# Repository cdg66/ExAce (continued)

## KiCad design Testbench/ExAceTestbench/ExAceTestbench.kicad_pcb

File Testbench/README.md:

this is asimple board that breakout the SERDES pins out to SMA connectors for easy testing of the interface.

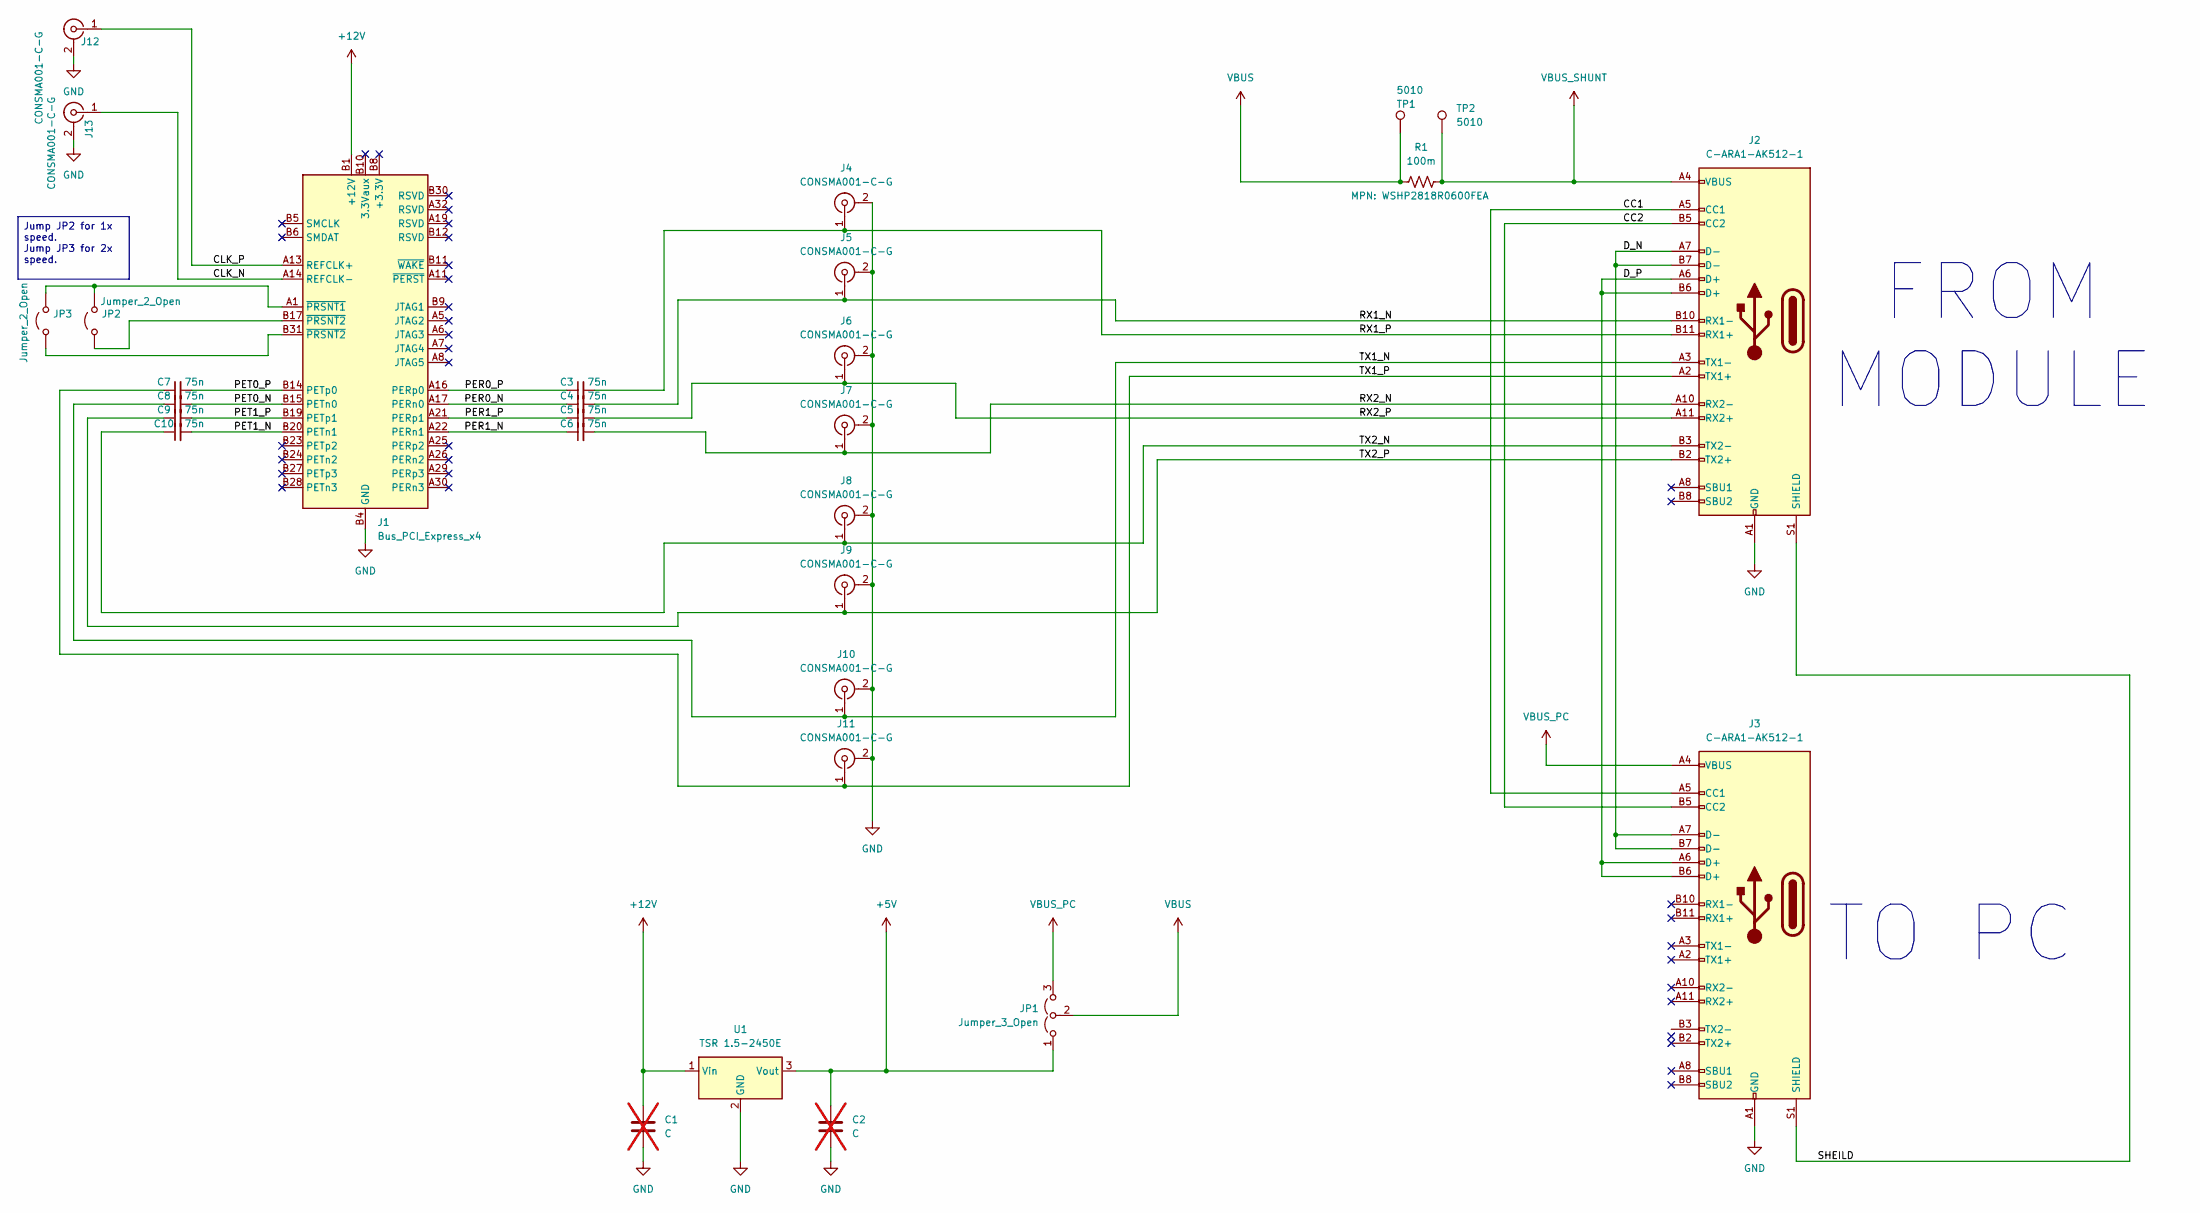
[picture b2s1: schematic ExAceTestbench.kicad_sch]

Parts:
C1, C2: C; C_1206_3216Metric; not fitted
C3, C4, C5, C6, C7, C8, C9, C10: 75n; C_0402_1005Metric
J1: Bus_PCI_Express_x4; BUS_PCIexpress_x4
J2, J3: C-ARA1-AK512-1; USB_C_Receptacle_CNCTech_C-ARA1-AK51X; MPN C-ARA1-AK512-1
J4, J5, J6, J7, J8, J9, J10, J11, J12, J13: CONSMA001-C-G; SMA_Amphenol_901-144_Vertical; MPN CONSMA001-C-G
JP1: Jumper_3_Open; PinHeader_1x03_P2.54mm_Vertical
JP2, JP3: Jumper_2_Open; PinHeader_1x02_P2.54mm_Vertical
R1: 100m; 2818; MPN WSHP2818R0600FEA
TP1, TP2: 5010; TestPoint_Keystone_5010-5014_Multipurpose; MPN 5010
U1: TSR 1.5-2450E; Converter_DCDC_TRACO_TSR-1_THT

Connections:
+5V: C2.1, JP1.1 (A), U1.3 (Vout)
+12V: C1.1, J1.A2 (+12V), J1.A3 (+12V), J1.B1 (+12V), J1.B2 (+12V), J1.B3 (+12V), U1.1 (Vin)
/CC1: J2.A5 (CC1), J3.A5 (CC1)
/CC2: J2.B5 (CC2), J3.B5 (CC2)
/CLK_N: J1.A14 (REFCLK-), J13.1 (In)
/CLK_P: J1.A13 (REFCLK+), J12.1 (In)
/D_N: J2.A7 (D-), J2.B7 (D-), J3.A7 (D-), J3.B7 (D-)
/D_P: J2.A6 (D+), J2.B6 (D+), J3.A6 (D+), J3.B6 (D+)
/PER0_N: C4.1, J1.A17 (PERn0)
/PER0_P: C3.1, J1.A16 (PERp0)
/PER1_N: C6.1, J1.A22 (PERn1)
/PER1_P: C5.1, J1.A21 (PERp1)
/PET0_N: C8.2, J1.B15 (PETn0)
/PET0_P: C7.2, J1.B14 (PETp0)
/PET1_N: C10.2, J1.B20 (PETn1)
/PET1_P: C9.2, J1.B19 (PETp1)
/RX1_N: C4.2, J2.B10 (RX1-), J5.1 (In)
/RX1_P: C3.2, J2.B11 (RX1+), J4.1 (In)
/RX2_N: C6.2, J2.A10 (RX2-), J7.1 (In)
/RX2_P: C5.2, J2.A11 (RX2+), J6.1 (In)
/SHEILD: J2.S1 (SHIELD), J3.S1 (SHIELD)
/TX1_N: C8.1, J2.A3 (TX1-), J10.1 (In)
/TX1_P: C7.1, J2.A2 (TX1+), J11.1 (In)
/TX2_N: C10.1, J2.B3 (TX2-), J8.1 (In)
/TX2_P: C9.1, J2.B2 (TX2+), J9.1 (In)
GND: C1.2, C2.2, J1.A4 (GND), J1.A12 (GND), J1.A15 (GND), J1.A18 (GND), J1.A20 (GND), J1.A23 (GND), J1.A24 (GND), J1.A27 (GND), J1.A28 (GND), J1.A31 (GND), J1.B4 (GND), J1.B7 (GND), J1.B13 (GND), J1.B16 (GND), J1.B18 (GND), J1.B21 (GND), J1.B22 (GND), J1.B25 (GND), J1.B26 (GND), J1.B29 (GND), J1.B32 (GND), J2.A1 (GND), J2.A12 (GND), J2.B1 (GND), J2.B12 (GND), J3.A1 (GND), J3.A12 (GND), J3.B1 (GND), J3.B12 (GND), J4.2 (Ext), J5.2 (Ext), J6.2 (Ext), J7.2 (Ext), J8.2 (Ext), J9.2 (Ext), J10.2 (Ext), J11.2 (Ext), J12.2 (Ext), J13.2 (Ext), U1.2 (GND)
unnamed: J1.A1 (~PRSNT1), JP2.2 (B), JP3.2 (B)
unnamed: J1.B17 (~PRSNT2), JP2.1 (A)
unnamed: J1.B31 (~PRSNT2), JP3.1 (A)
VBUS: JP1.2 (C), R1.1, TP1.1
VBUS_PC: J3.A4 (VBUS), J3.A9 (VBUS), J3.B4 (VBUS), J3.B9 (VBUS), JP1.3 (B)
VBUS_SHUNT: J2.A4 (VBUS), J2.A9 (VBUS), J2.B4 (VBUS), J2.B9 (VBUS), R1.2, TP2.1

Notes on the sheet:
FROM MODULE
TO PC
Jump JP2 for 1x speed. Jump JP3 for 2x speed.

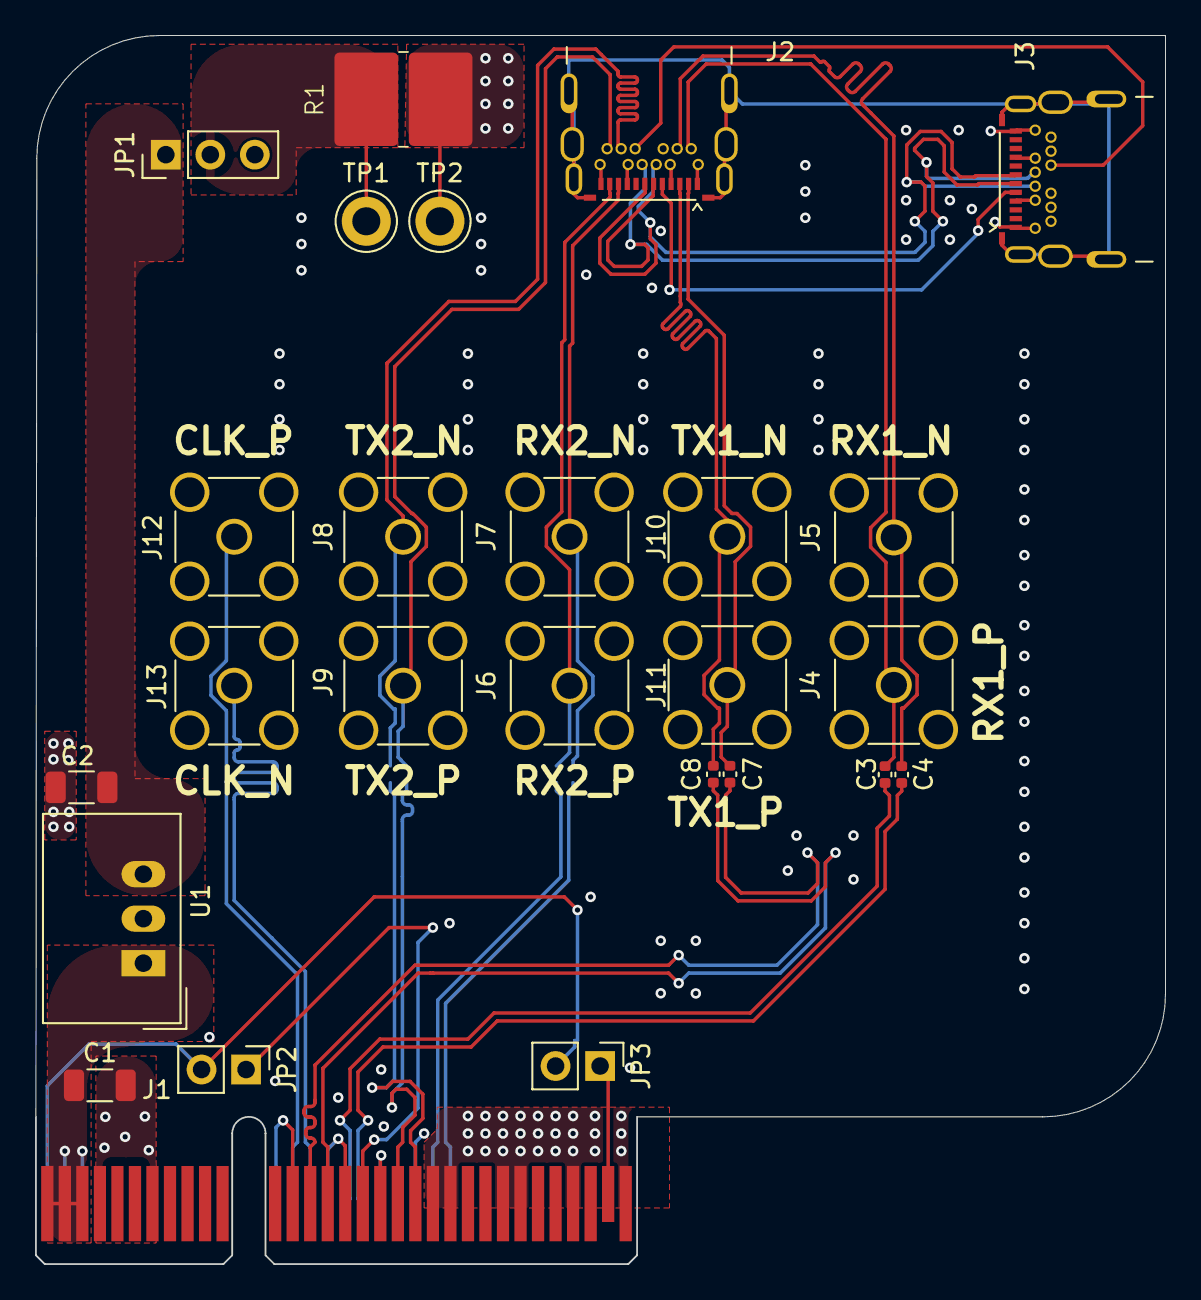
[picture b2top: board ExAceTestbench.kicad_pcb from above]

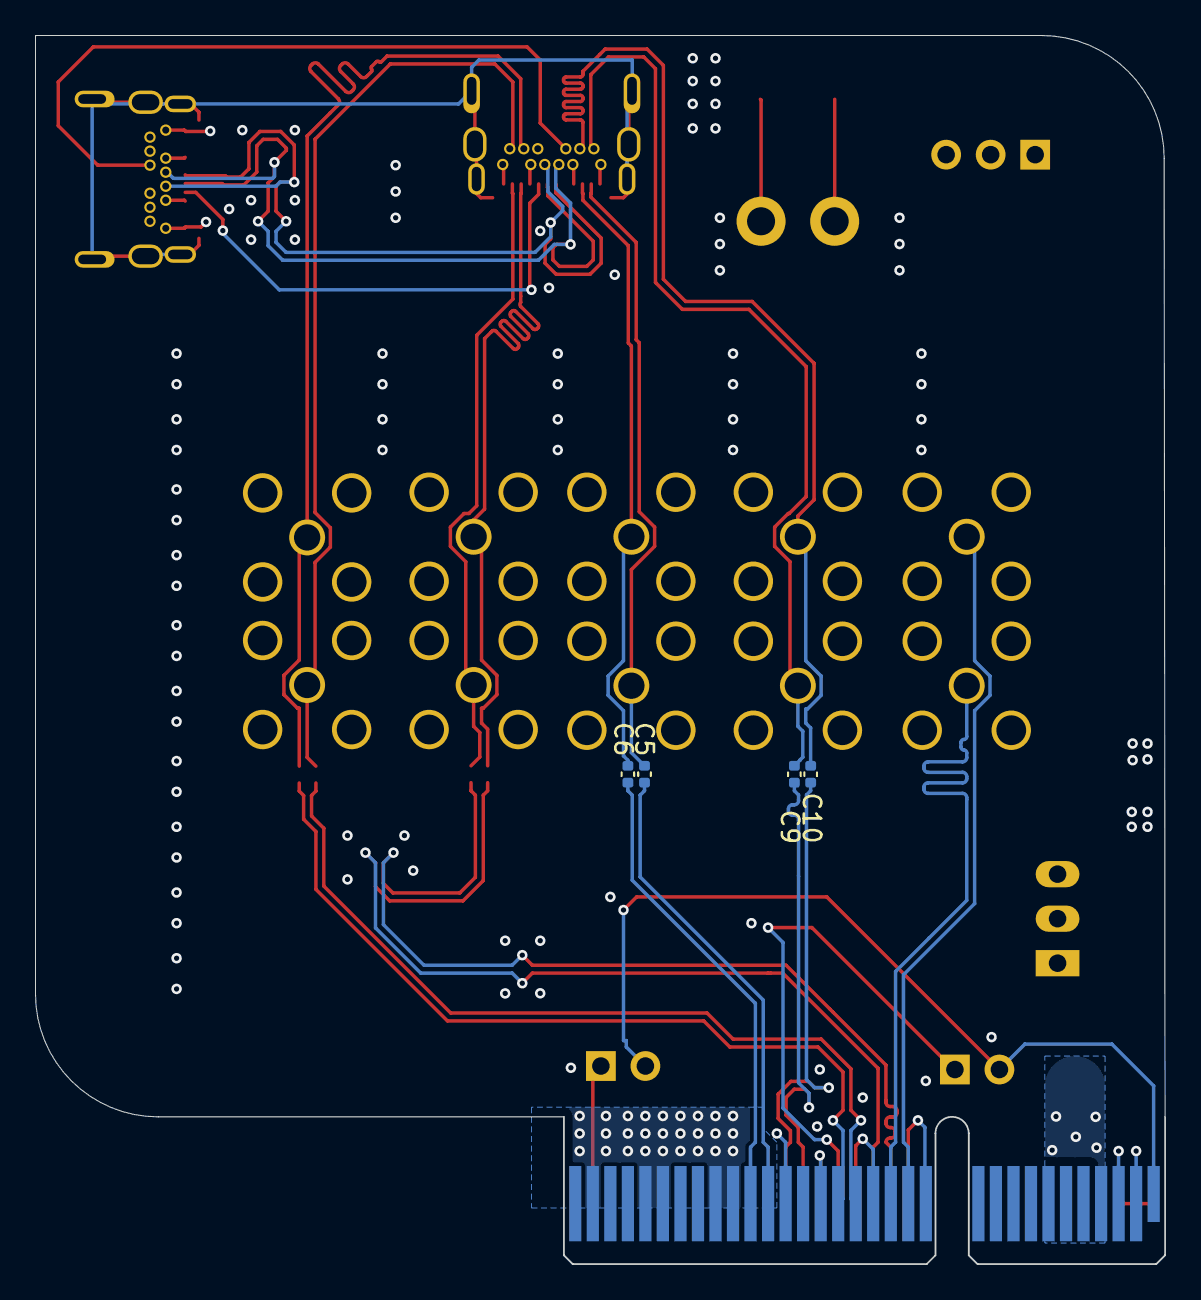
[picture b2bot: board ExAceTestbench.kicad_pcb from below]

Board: 4 copper layers, 64.5 x 70.1 mm, 30 parts (4 on the bottom side), 32 nets.

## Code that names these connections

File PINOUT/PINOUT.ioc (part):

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Mcu.Name=STM32L422RBIx
Mcu.Package=UFBGA64
Mcu.UserName=STM32L422RBIx
PA1.GPIOParameters=GPIO_Label
PA1.GPIO_Label=FPGA_RST
PA1.Signal=GPIO_Output
PA11.Mode=Device
PA11.Signal=USB_DM
PA12.Mode=Device
PA12.Signal=USB_DP
PA13\ (JTMS/SWDIO).Mode=Serial_Wire
PA13\ (JTMS/SWDIO).Signal=SYS_JTMS-SWDIO
PA14\ (JTCK/SWCLK).Mode=Serial_Wire
PA14\ (JTCK/SWCLK).Signal=SYS_JTCK-SWCLK
PA15\ (JTDI).GPIOParameters=GPIO_Label
PA15\ (JTDI).GPIO_Label=CFG1
PA15\ (JTDI).Signal=GPIO_Output
PA2.Mode=Single Bank 1
PA2.Signal=QUADSPI_BK1_NCS
PA3.Mode=Single Bank 1
PA3.Signal=QUADSPI_CLK
PA6.Mode=Single Bank 1
PA6.Signal=QUADSPI_BK1_IO3
PA7.Mode=Single Bank 1
PA7.Signal=QUADSPI_BK1_IO2
PA8.Mode=Clock-out
PA8.Signal=RCC_MCO
PB0.Mode=Single Bank 1
PB0.Signal=QUADSPI_BK1_IO1
PB1.Mode=Single Bank 1
PB1.Signal=QUADSPI_BK1_IO0
PB10.Mode=Asynchronous
PB10.Signal=LPUART1_RX
PB11.Mode=Asynchronous
PB11.Signal=LPUART1_TX
PB12.GPIOParameters=GPIO_Label
PB12.GPIO_Label=USB_PU
PB12.Signal=GPIO_Input
PB13.Mode=I2C
PB13.Signal=I2C2_SCL
PB14.Mode=I2C
PB14.Signal=I2C2_SDA
PB3\ (JTDO/TRACESWO).GPIOParameters=GPIO_Label
PB3\ (JTDO/TRACESWO).GPIO_Label=CFG0
PB3\ (JTDO/TRACESWO).Signal=GPIO_Output
PB4\ (NJTRST).GPIOParameters=GPIO_Label
PB4\ (NJTRST).GPIO_Label=CFG2
PB4\ (NJTRST).Signal=GPIO_Output
PB9.GPIOParameters=GPIO_Label
PB9.GPIO_Label=CFG3
PB9.Signal=GPIO_Output
PC14-OSC32_IN\ (PC14).GPIOParameters=GPIO_Label
PC14-OSC32_IN\ (PC14).GPIO_Label=TCK
PC14-OSC32_IN\ (PC14).Signal=GPIO_Output
PC15-OSC32_OUT\ (PC15).GPIOParameters=GPIO_Label
PC15-OSC32_OUT\ (PC15).GPIO_Label=TMS
PC15-OSC32_OUT\ (PC15).Signal=GPIO_Output
PH0-OSC_IN\ (PH0).Mode=HSE-External-Clock-Source
PH0-OSC_IN\ (PH0).Signal=RCC_OSC_IN
RCC.HSE_VALUE=8000000
RCC.SYSCLKFreq_VALUE=80000000
RCC.SYSCLKSource=RCC_SYSCLKSOURCE_PLLCLK
board=custom

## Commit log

2025-03-15 first routing
2025-03-21 Layout and add sensor
2025-03-29 update on layout first drc done
2025-04-28 start to switch to stm32
2025-04-29 draft layout
2025-05-03 testbench done
2025-05-06 fixed diff pair
2025-05-17 RevA
2025-05-17 removing old file
2025-05-17 remove some unused files
2025-05-17 remove unused pdf
2025-05-21 add readme
2025-05-21 fix wording and remove unused models
2025-05-24 add stackup to readme
2025-05-24 fix formating
2025-05-31 Create README.md
    add testbench simple description
2025-06-03 Fix typo on README.md
2025-06-04 fix a clearance issue
2025-06-04 fix clearance on R4
